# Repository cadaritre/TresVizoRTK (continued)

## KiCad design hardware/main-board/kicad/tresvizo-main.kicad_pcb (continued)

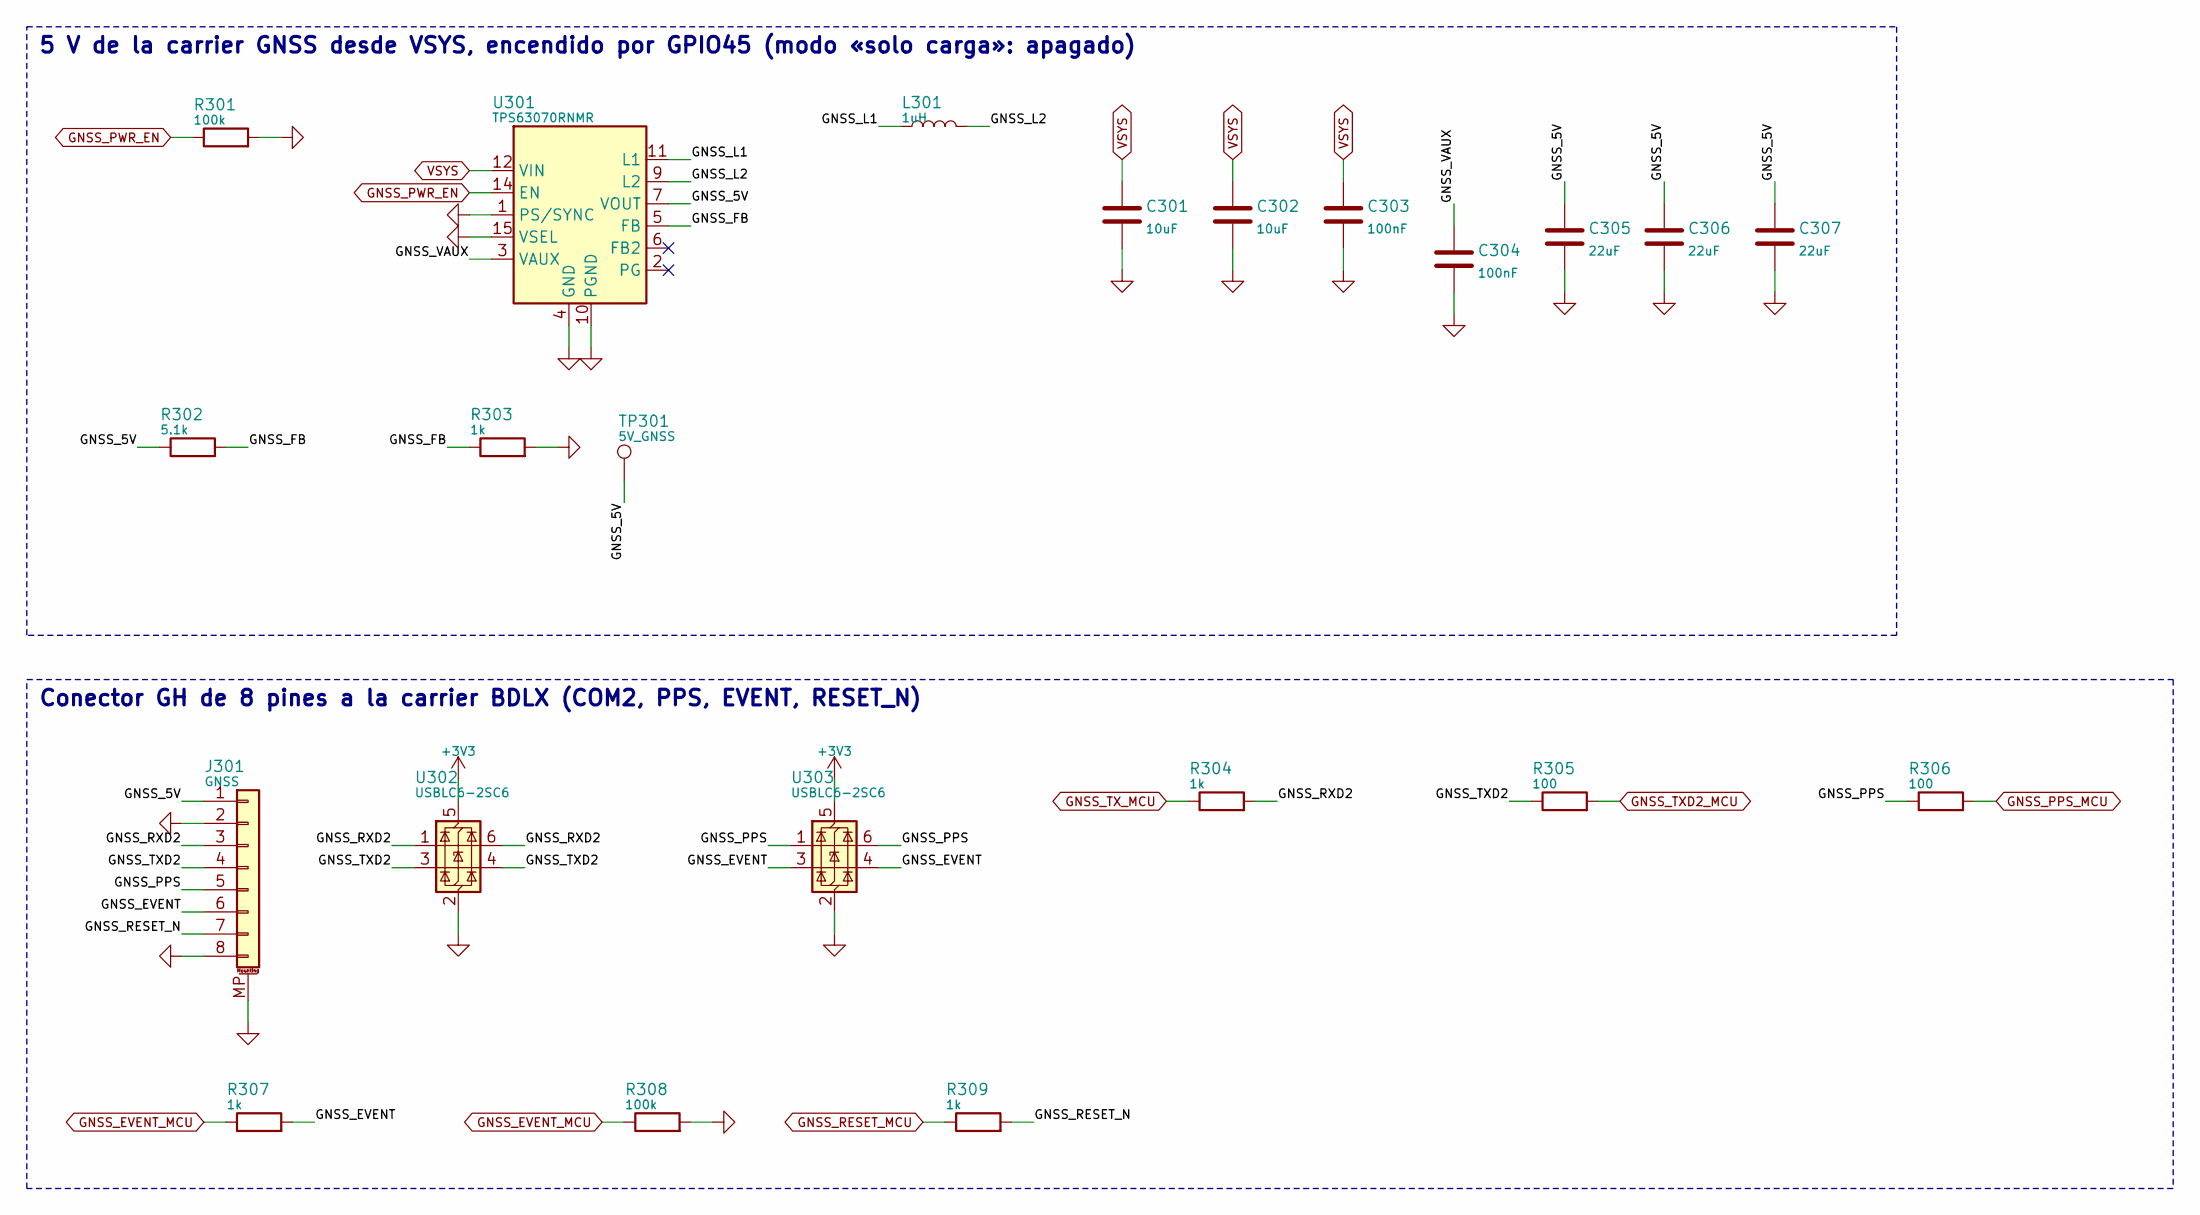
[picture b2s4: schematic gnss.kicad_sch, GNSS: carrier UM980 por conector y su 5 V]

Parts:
C301, C302: 10uF; C_0805_2012Metric; MPN CL21A106KAYNNNE; LCSC C15850
C303, C304: 100nF; C_0402_1005Metric; MPN CL05B104KB54PNC; LCSC C307331
C305, C306, C307: 22uF; C_0805_2012Metric; MPN CL21A226MAQNNNE; LCSC C45783
J301: GNSS; CONN-TH_SM08B-SRSS-TB-LF-SN; MPN SM08B-SRSS-TB(LF)(SN); LCSC C160407
L301: 1uH; L2520; MPN DFE252012F-1R0M=P2; LCSC C435392
R301, R308: 100k; R_0402_1005Metric; MPN 0402WGF1003TCE; LCSC C25741
R302: 5.1k; R_0402_1005Metric; MPN 0402WGF5101TCE; LCSC C25905
R303, R304, R307, R309: 1k; R_0402_1005Metric; MPN 0402WGF1001TCE; LCSC C11702
R305, R306: 100; R_0402_1005Metric; MPN 0402WGF1000TCE; LCSC C25076
TP301: 5V_GNSS; TestPoint_Pad_D1.0mm
U301: TPS63070RNMR; VQFN-15_L3.0-W2.5-P0.50-BL; MPN TPS63070RNMR; LCSC C109322
U302, U303: USBLC6-2SC6; SOT-23-6_L2.9-W1.6-P0.95-LS2.8-BL; MPN USBLC6-2SC6; LCSC C2687116

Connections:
/GNSS: carrier UM980 por conector y su 5 V/GNSS_5V: C305.1, C306.1, C307.1, J301.1, R302.1, TP301.1, U301.7 (VOUT)
/GNSS: carrier UM980 por conector y su 5 V/GNSS_EVENT: J301.6, R307.2, U303.3 (I/O2), U303.4 (I/O2)
/GNSS: carrier UM980 por conector y su 5 V/GNSS_FB: R302.2, R303.1, U301.5 (FB)
/GNSS: carrier UM980 por conector y su 5 V/GNSS_L1: L301.1, U301.11 (L1)
/GNSS: carrier UM980 por conector y su 5 V/GNSS_L2: L301.2, U301.9 (L2)
/GNSS: carrier UM980 por conector y su 5 V/GNSS_PPS: J301.5, R306.1, U303.1 (I/O1), U303.6 (I/O1)
/GNSS: carrier UM980 por conector y su 5 V/GNSS_RESET_N: J301.7, R309.2
/GNSS: carrier UM980 por conector y su 5 V/GNSS_RXD2: J301.3, R304.2, U302.1 (I/O1), U302.6 (I/O1)
/GNSS: carrier UM980 por conector y su 5 V/GNSS_TXD2: J301.4, R305.1, U302.3 (I/O2), U302.4 (I/O2)
/GNSS: carrier UM980 por conector y su 5 V/GNSS_VAUX: C304.1, U301.3 (VAUX)
GNSS_EVENT_MCU: R307.1, R308.1; also elsewhere on the board
GNSS_PPS_MCU: R306.2; also elsewhere on the board
GNSS_PWR_EN: R301.1, U301.14 (EN); also elsewhere on the board
GNSS_RESET_MCU: R309.1; also elsewhere on the board
GNSS_TXD2_MCU: R305.2; also elsewhere on the board
GNSS_TX_MCU: R304.1; also elsewhere on the board
VSYS: C301.1, C302.1, C303.1, U301.12 (VIN); also elsewhere on the board

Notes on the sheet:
5 V de la carrier GNSS desde VSYS, encendido por GPIO45 (modo «solo carga»: apagado)
Conector GH de 8 pines a la carrier BDLX (COM2, PPS, EVENT, RESET_N)

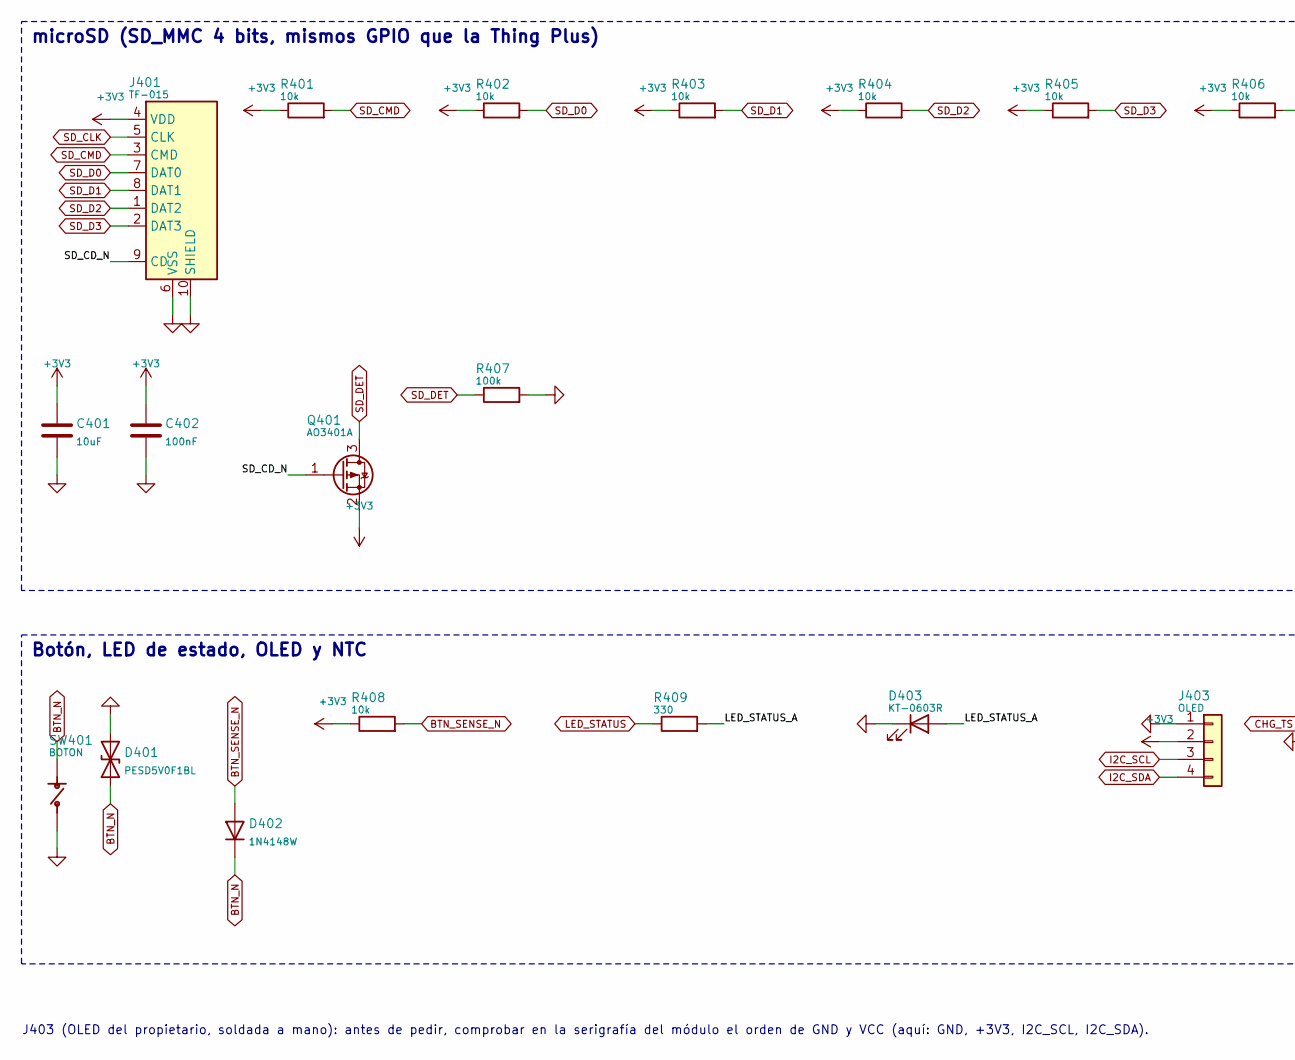
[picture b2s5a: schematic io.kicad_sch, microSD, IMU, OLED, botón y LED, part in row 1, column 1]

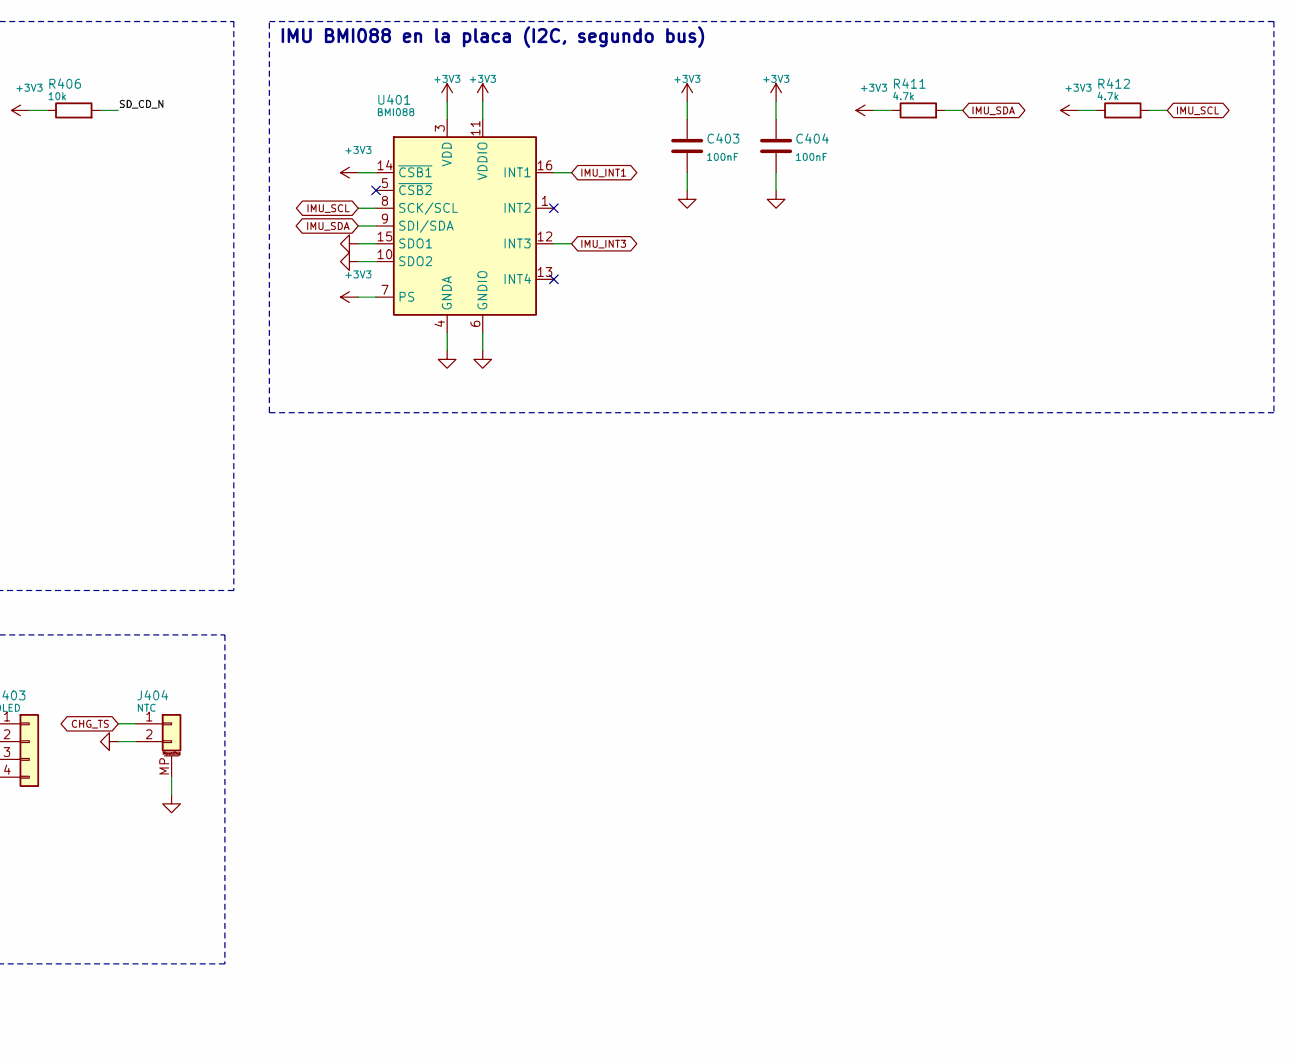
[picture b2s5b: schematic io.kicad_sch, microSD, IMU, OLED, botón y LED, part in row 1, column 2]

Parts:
C401: 10uF; C_0805_2012Metric; MPN CL21A106KAYNNNE; LCSC C15850
C402, C403, C404: 100nF; C_0402_1005Metric; MPN CL05B104KB54PNC; LCSC C307331
D401: PESD5V0F1BL; SOD-882_L1.0-W0.6-BI; MPN PESD5V0F1BL; LCSC C3001950
D402: 1N4148W; SOD-123F_L2.7-W1.6-LS3.8-RD; MPN 1N4148W; LCSC C81598
D403: KT-0603R; LED-SMD_L1.6-W0.8-R-RD; MPN KT-0603R; LCSC C2286
J401: TF-015; TF-SMD_TF-015; MPN TF-015; LCSC C113206
J403: OLED; OLED_0.96in_I2C_4P_P2.54mm
J404: NTC; CONN-SMD_2P-P1.00_SM02B-SRSS-TB-LF-SN; MPN SM02B-SRSS-TB(LF)(SN); LCSC C160402
Q401: AO3401A; SOT-23_L2.9-W1.3-P1.90-LS2.4-BR; MPN AO3401A; LCSC C15127
R401, R402, R403, R404, R405, R406, R408: 10k; R_0402_1005Metric; MPN 0402WGF1002TCE; LCSC C25744
R407: 100k; R_0402_1005Metric; MPN 0402WGF1003TCE; LCSC C25741
R409: 330; R_0402_1005Metric; MPN 0402WGF3300TCE; LCSC C25104
R411, R412: 4.7k; R_0402_1005Metric; MPN 0402WGF4701TCE; LCSC C25900
SW401: BOTON; SW-SMD_4P-L5.1-W5.1-P3.70-LS6.5-TL_H1.5; MPN TS-1187A-B-A-B; LCSC C318884
U401: BMI088; LGA-16_L4.5-W3.0-P0.50-BL; MPN BMI088; LCSC C194919

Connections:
/microSD, IMU, OLED, botón y LED/LED_STATUS_A: D403.2 (A), R409.2
/microSD, IMU, OLED, botón y LED/SD_CD_N: J401.9 (CD), Q401.1 (G), R406.2
BTN_N: D401.1 (A1), D402.1 (K), SW401.1 (A); also elsewhere on the board
BTN_SENSE_N: D402.2 (A), R408.2; also elsewhere on the board
CHG_TS: J404.1; also elsewhere on the board
I2C_SCL: J403.3; also elsewhere on the board
I2C_SDA: J403.4; also elsewhere on the board
IMU_INT1: U401.16 (INT1); also elsewhere on the board
IMU_INT3: U401.12 (INT3); also elsewhere on the board
IMU_SCL: R412.2, U401.8 (SCK/SCL); also elsewhere on the board
IMU_SDA: R411.2, U401.9 (SDI/SDA); also elsewhere on the board
SD_CLK: J401.5 (CLK); also elsewhere on the board
SD_CMD: J401.3 (CMD), R401.2; also elsewhere on the board
SD_D0: J401.7 (DAT0), R402.2; also elsewhere on the board
SD_D1: J401.8 (DAT1), R403.2; also elsewhere on the board
SD_D2: J401.1 (DAT2), R404.2; also elsewhere on the board
SD_D3: J401.2 (DAT3), R405.2; also elsewhere on the board
SD_DET: Q401.3 (D), R407.1; also elsewhere on the board

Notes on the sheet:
microSD (SD_MMC 4 bits, mismos GPIO que la Thing Plus)
IMU BMI088 en la placa (I2C, segundo bus)
Botón, LED de estado, OLED y NTC
J403 (OLED del propietario, soldada a mano): antes de pedir, comprobar en la serigrafía del módulo el orden de GND y VCC (aquí: GND, +3V3, I2C_SCL, I2C_SDA).

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
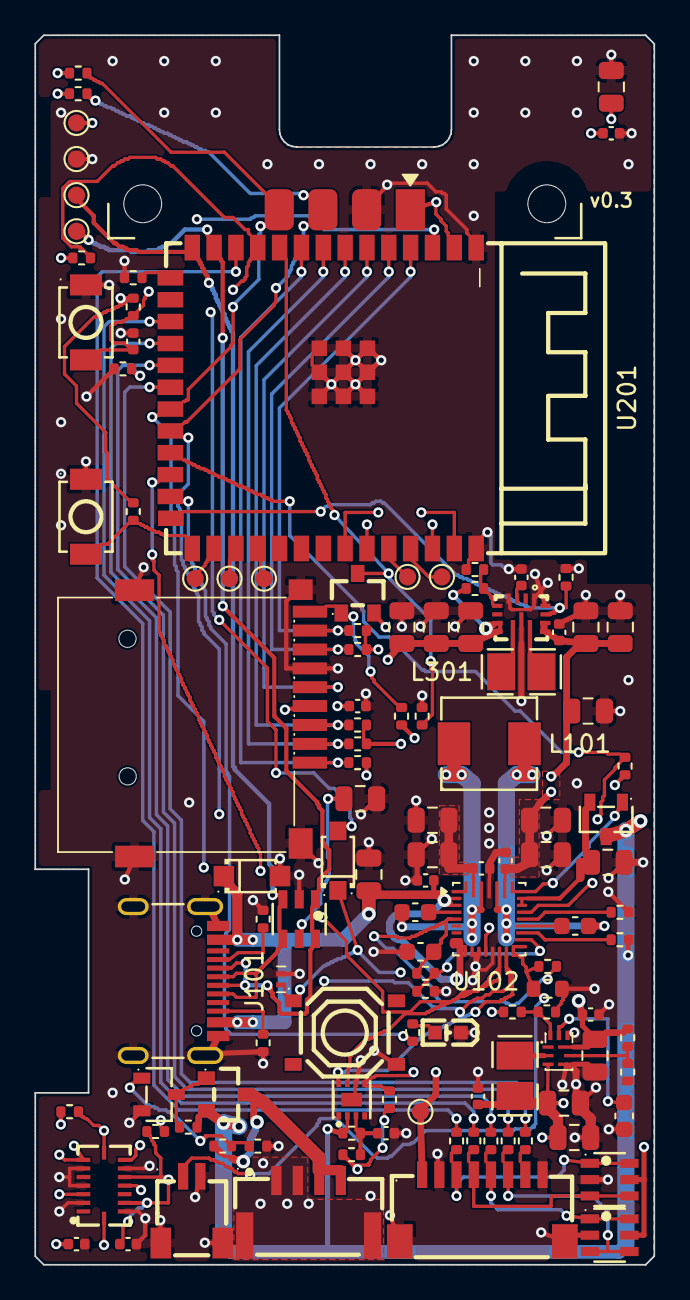
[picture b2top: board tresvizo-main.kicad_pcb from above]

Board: 4 copper layers, 36.0 x 71.5 mm, 117 parts (0 on the bottom side), 73 nets.

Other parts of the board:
TP208: U0TXD; TestPoint_Pad_D1.0mm
TP209: U0RXD; TestPoint_Pad_D1.0mm

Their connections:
/ESP32-S3/ESP_RXD0: TP209.1; also elsewhere on the board
/ESP32-S3/ESP_TXD0: TP208.1; also elsewhere on the board

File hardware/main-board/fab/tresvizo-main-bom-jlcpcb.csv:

Comment,Designator,Footprint,LCSC Part #
47nF,"C101,C102,C117",C_0603_1608Metric,C1622
4.7uF,C103,C_0603_1608Metric,C19666
22uF,"C104,C106,C107,C109,C110,C113,C118,C119,C201,C305,C306,C307",C_0805_2012Metric,C45783
100nF,"C105,C108,C112,C114,C116,C120,C202,C303,C304,C402,C403,C404",C_0402_1005Metric,C307331
10uF,"C111,C115,C301,C302,C401",C_0805_2012Metric,C15850
SMF15A,D101,SOD-123FL_L2.7-W1.8-LS3.8-RD,C19077509
USB_C,J101,USB-C_SMD-TYPE-C-31-M-12,C165948
BATTERY,J102,CONN-SMD_4P-P1.25_SM04B-GHS-TB-LF-SN,C189895
2.2uH,L101,IND-SMD_L5.4-W5.2,C408408
1uH,"L102,L301",L2520,C435392
AO3400A,"Q101,Q103",SOT-23-3_L2.9-W1.3-P1.90-LS2.4-BR,C20917
AO3401A,"Q102,Q401",SOT-23_L2.9-W1.3-P1.90-LS2.4-BR,C15127
10k,"R101,R108,R113,R116,R201,R202,R203,R401,R402,R403,R404,R405,R406,R408",R_0402_1005Metric,C25744
8.2k,R102,R_0402_1005Metric,C25924
4.7k,"R103,R204,R205,R411,R412",R_0402_1005Metric,C25900
5.1k,"R104,R119,R120,R302",R_0402_1005Metric,C25905
30k,R105,R_0603_1608Metric,C22984
100,"R107,R305,R306",R_0402_1005Metric,C25076
1M,"R109,R111",R_0402_1005Metric,C26083
100k,"R110,R117,R301,R308,R407",R_0402_1005Metric,C25741
0,R112,R_0402_1005Metric,C17168
22k,"R115,R118",R_0402_1005Metric,C25768
USBLC6-2SC6,"U101,U302,U303",SOT-23-6_L2.9-W1.6-P0.95-LS2.8-BL,C2687116
BQ25798RQMR,U102,Texas_RQM0029A_VQFN-29_4x4mm_P0.4mm,C2876593
MAX17048G+T10,U103,TDFN-8_L2.0-W2.0-P0.50-BL-EP1.2,C2682616
TPS62903RPJR,U105,VQFN-HR-9_L2.0-W1.5-P0.50-TL,C2866502
1uF,C203,C_0402_1005Metric,C52923
BOOT/RESET,"SW201,SW202",SW-SMD_L3.9-W3.0-P4.45,C720477
ESP32-S3-WROOM-1-N16R2,U201,WIRELM-SMD_ESP32-S3-WROOM-1,C2913205
GNSS,J301,CONN-TH_SM08B-SRSS-TB-LF-SN,C160407
1k,"R303,R304,R307,R309",R_0402_1005Metric,C11702
TPS63070RNMR,U301,VQFN-15_L3.0-W2.5-P0.50-BL,C109322
PESD5V0F1BL,D401,SOD-882_L1.0-W0.6-BI,C3001950
1N4148W,D402,SOD-123F_L2.7-W1.6-LS3.8-RD,C81598
KT-0603R,D403,LED-SMD_L1.6-W0.8-R-RD,C2286
TF-015,J401,TF-SMD_TF-015,C113206
NTC,J404,CONN-SMD_2P-P1.00_SM02B-SRSS-TB-LF-SN,C160402
330,R409,R_0402_1005Metric,C25104
BOTON,SW401,SW-SMD_4P-L5.1-W5.1-P3.70-LS6.5-TL_H1.5,C318884
BMI088,U401,LGA-16_L4.5-W3.0-P0.50-BL,C194919

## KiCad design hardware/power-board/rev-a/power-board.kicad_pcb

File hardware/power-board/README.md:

> **PCB PERSONALIZADA CANCELADA — 20-09-2026.** Por indicación del propietario se retiraron sólo los archivos de diseño PCB, sus generadores y salidas de fabricación. Se conserva la documentación y los datasheets como antecedentes; los enlaces a archivos eliminados de abajo ya no son entregables vigentes. La propuesta actual utiliza [módulos comerciales](../power-modules/README.md). El case y el firmware no se modificaron en esta sustitución.

# Power & Interface Board — Rev A

Diseño digital del prototipo terminado: esquema jerárquico de ocho hojas y PCB **45 × 40 × 1.6 mm**, cuatro capas, montaje en ambas caras. Contiene 149 referencias eléctricas y 135 componentes poblados. USB nativo de la Tiny externa; ESP32, UM980 e IMU permanecen fuera de esta placa. CP2102N eliminado. Revisión del 20 de septiembre de 2026.

- [Proyecto KiCad 10](rev-a/power-board.kicad_pro), [esquema editable](rev-a/power-board.kicad_sch), [PDF de 8 hojas](rev-a/output/pdf/power-board.pdf) y [PCB ruteado](rev-a/power-board.kicad_pcb).
- [Vista 3D](rev-a/review/power-board-3d.png), [cara inferior](rev-a/review/power-board-bottom.png) y [mapas de componentes](rev-a/review/assembly-top.svg).
- [Decisiones de diseño](rev-a/DESIGN.md), [potencia](POWER_BUDGET.md), [conexiones y firmware](rev-a/INTERFACES.md).
- [BOM](manufacturing/rev-a/assembly/bom.csv), [BOM JLCPCB](manufacturing/rev-a/assembly/bom-jlcpcb.csv), [CPL](manufacturing/rev-a/assembly/cpl-jlcpcb.csv) y [notas de compra](bom.md).
- [Fabricación](rev-a/MANUFACTURING.md), [pruebas del prototipo](rev-a/BRINGUP.md) y [verificación realizada](VALIDATION.md).
- [STEP de integración](manufacturing/power-board.step), [JSON mecánico](../../mechanical/integration/power_board_interface.json) y [guía FreeCAD](../../mechanical/integration/POWER_BOARD_INTEGRATION.md).
- [Paquete completo ZIP](manufacturing/power-board-rev-a.zip).

**ERC: 0 incidencias. DRC: 0 incidencias, 0 conexiones pendientes y 0 diferencias esquema–PCB.** Auditoría adicional: 450 conexiones comprobadas y cálculo de márgenes USB. Son verificaciones digitales; no ensayos eléctricos.

J5 queda como **FPC candidato DNP**, sin montar hasta contrastar contactos, orientación y continuidad con la unidad real. La BOM identifica datos comerciales sin confirmar. El prototipo requiere DFM del ensamblador, NTC externo en la batería y pruebas eléctricas/térmicas/USB/mecánicas antes de liberar producción. No se ha pedido fabricación.

`rev-a/` es la revisión vigente. `kicad/`, DESIGN_D0.md y la investigación P1 se conservan como antecedentes, no para fabricación. El propietario autorizó diseño compacto y adaptación mecánica posterior por el responsable de la carcasa.

Fuentes versionables: `rev-a/circuit.json`, `tools/design_rev_a.py`, `tools/render_rev_a.py` y el PCB KiCad ruteado. Se empleó KiCad directamente; no depende de una compilación atopile no comprobada. **No ejecutar layout_rev_a.py sobre el PCB final: es un generador de placement inicial.** La reexportación segura está documentada en MANUFACTURING.md.

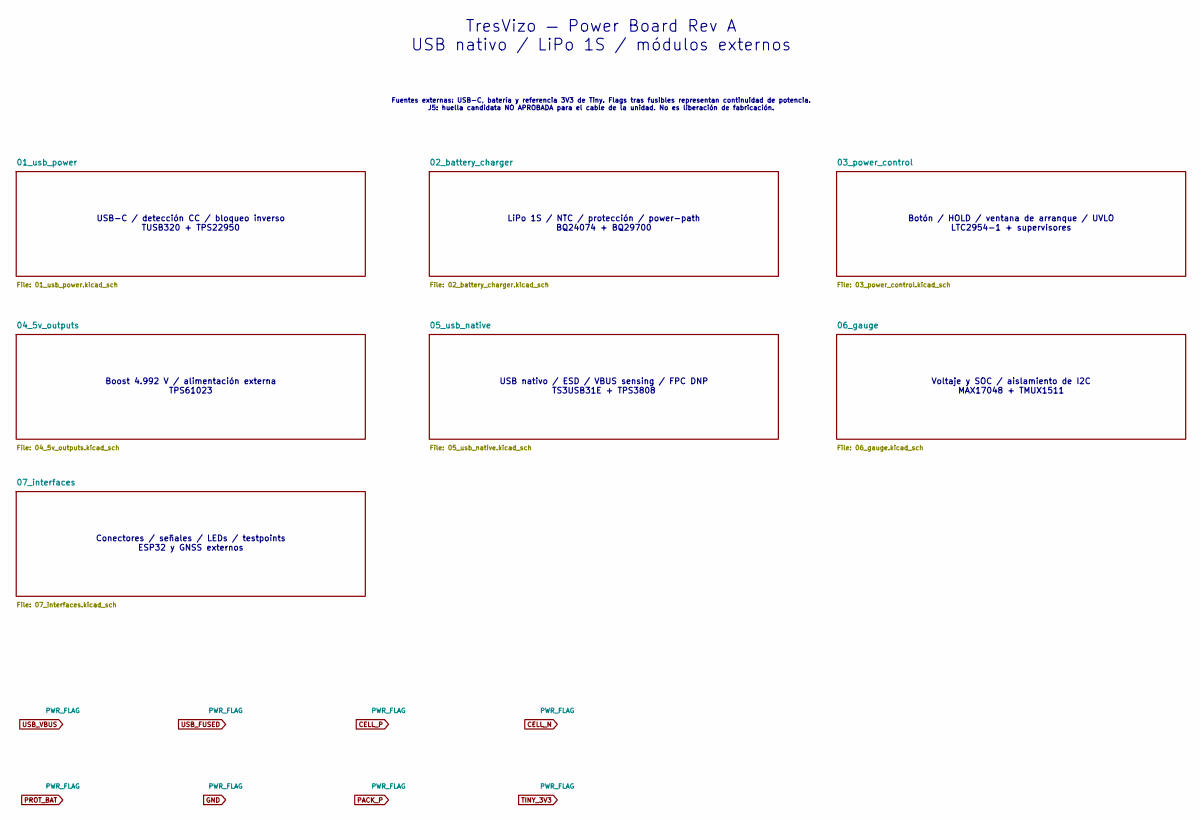
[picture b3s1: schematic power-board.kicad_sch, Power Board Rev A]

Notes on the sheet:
USB-C / detección CC / bloqueo inverso TUSB320 + TPS22950
LiPo 1S / NTC / protección / power-path BQ24074 + BQ29700
Botón / HOLD / ventana de arranque / UVLO LTC2954-1 + supervisores
Boost 4.992 V / alimentación externa TPS61023
USB nativo / ESD / VBUS sensing / FPC DNP TS3USB31E + TPS3808
Voltaje y SOC / aislamiento de I2C MAX17048 + TMUX1511
Conectores / señales / LEDs / testpoints ESP32 y GNSS externos
TresVizo — Power Board Rev A USB nativo / LiPo 1S / módulos externos
Fuentes externas: USB-C, batería y referencia 3V3 de Tiny. Flags tras fusibles representan continuidad de potencia. J5: huella candidata NO APROBADA para el cable de la unidad. No es liberación de fabricación.
